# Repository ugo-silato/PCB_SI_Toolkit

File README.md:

# PCB Signal Integrity Toolkit for KiCad
<!-- Donation button: opens my Ko-fi page ("Buy me a Transistor") -->
<!-- The SVG image is hosted in my .github repository, so every README uses the same file -->
<p align="center">
  
</p>

<!-- Short note shown below the button -->
<p align="center">
  Free and open source. If this tool saved you some time,<br>
  a transistor helps me keep developing and sharing new ones ⚡
</p>

A KiCad 10 plugin (Pcbnew) that brings together signal- and power-integrity checks on the board you are designing:

| Tab | What it does |
|---|---|
| **Layout checks** | A smart DRC on the whole board: distance of the decoupling capacitors from the IC supply pins and their ground vias, signal vias that change reference plane without a ground via nearby, stitching via spacing on multi-layer ground, tracks over plane gaps, tracks close to the edge of their reference plane, track width against the current (IPC-2221), isolation between nets above 30 V (IPC-2221), length difference of differential pairs and net groups, dead branches, acute angles, width steps, vias in SMD pads, tombstoning risk, number of vias for the current, crystal placement, overlapping tracks on adjacent layers. Every row is a measure compared with a threshold, marked on the board |
| **Return Path** | Finds tracks that cross gaps in the reference plane underneath, and marks them on the board. **Return map** (HF and DC) shows where the return current of a line flows in the ground, from its loads to the chosen ground exit |
| **DC Current** | Solves the resistive network of tracks and vias: current, IR drop, density and IPC-2221 limit, with one or more loads and a color map |
| **Impedance** | Z0 of every track with a 2D field solver, from the real board stackup (coplanar ground, solder mask) |
| **Diff. pairs** | Differential and common-mode impedance with the field solver (odd/even modes) |
| **Crosstalk** | Parallel runs between different nets and estimated NEXT |
| **openEMS** | 3D FDTD electromagnetic simulation of a line with [openEMS](https://www.openems.de): S-parameters, impedance, TDR/TDT and animated field GIFs |

The interface is available in **English** and **Italian** (Options tab), and every tab has a **?** button with an explanatory drawing.

## Return current map

Give the pad where the current enters and the ground pad where it leaves the board (e.g. the supply ground): the plugin finds the net and every load with a ground pin, also beyond series parts, estimates the current of each one from its type and value (TVS 0, resistor V/R, capacitor V/|Z|, MOSFET gate almost 0, collector V/(series R + pull-up) ...) and lets you check and correct it in a table. The map then shows, layer by layer, where the return flows in planes, coplanar ground and vias, at high frequency (it follows the track) or in DC (minimum resistance), with the share of every ground pin and via. Components and the tracks of the other nets can be drawn over the map to find your way. The currents are an estimate, not a circuit simulation: the result is theoretical.

## Layout checks

A smart DRC that **measures** the layout instead of predicting physical quantities: every row of the table is a fact about the board, with the **Measured** value next to the **Limit** it is compared with, a circle on the board (User.1 = errors, User.2 = warnings) and, for the plane edge, the measured segment with its value. Clicking a row selects the objects in Pcbnew. Currents, voltages and length groups are typed in the tab as `net = value; ...` (wildcards `*` and `?` allowed).

- **Exclude a row**: right click → *Exclude (accepted)*. The row turns grey and goes to the bottom, as KiCad does with excluded DRC errors; it is not counted and not drawn on the board, and it stays excluded in the next runs until the objects involved are edited.
- **Per-board data**: excluded rows and net data are saved next to the board in `board_name.si_toolkit.json`; thresholds stay global.
- **Report**: *Report...* writes `board_name_layout_checks.html` next to the board, with summary, thresholds, a drawing of the board with numbered problems and a zoomed drawing for every problem (print it to PDF from the browser).
- **Test board**: `docs/test_board` has a board with one case for each check and the list of expected rows.

| | |
|---|---|
|  |  |

| | |
|---|---|
| <br>**Plane edge**: Measured = from the edge of the track to where the ground copper of the adjacent layer really ends; Limit = 3 × h (dielectric height). Holes around pads/vias and narrow cuts made by tracks of the plane layer are not an edge. | <br>**Track width**: Measured = actual width; Limit = IPC-2221 width for the current of the net and the allowed temperature rise. |
| <br>**Isolation**: Measured = edge-to-edge copper distance on the same layer between nets more than 30 V apart; Limit = IPC-2221 table (B2 outer, B1 inner). | <br>**Lengths**: skew of the differential pairs (found from the names) and difference from the longest net of each group. |
| <br>**Dead branches**: tracks ending without connecting to anything; Measured = length of the dead branch. Tracks are connected when their copper touches, as in KiCad. | <br>**Acute angles**: segments of the same net meeting at less than 90° (acid traps); micro segments and overlaps are ignored. |
| <br>**Width steps**: a signal net with tracks of different widths on a layer; Measured = (wide − narrow) / narrow in %. Neck-downs at pads are ignored. | <br>**Vias in pads**: via drills inside SMD pads (solder wicking); large thermal pads are ignored. |
| <br>**Tombstoning**: small two-pad parts with one pad flooded in a zone and the other on a track. | <br>**Via current**: Measured = vias at a layer change, Limit = vias needed by IPC-2221 for the current of the net. |
| <br>**Crystal**: tracks of other nets under a crystal, and length of the crystal–IC tracks. | <br>**Overlapping tracks**: different nets one over the other on adjacent layers; Measured = overlap length. |

## Installation

### From the Plugin and Content Manager (recommended)
1. Download `si_toolkit_pcm_x.y.z.zip` from the [Releases](../../releases) page.
2. In KiCad open **Plugin and Content Manager → Install from File...**, choose the zip and press **Apply Pending Changes**.
3. Restart Pcbnew: the plugin appears in the toolbar and in **Tools → External Plugins**.

### Manually
Copy the `si_toolkit` folder into the KiCad user plugin folder, for example
`Documents\KiCad\10.0\scripting\plugins\si_toolkit`, then restart Pcbnew.

Settings are stored in the KiCad user configuration folder (`si_toolkit_settings.json`), so they survive plugin updates.

## openEMS (optional, only for the openEMS tab)
The plugin does **not** install openEMS. All other tabs work with KiCad's own Python.

1. Download openEMS for Windows from the official openEMS releases and extract it (e.g. `D:\Programs\openEMS`).
2. Install a 64-bit Python supported by that openEMS release.
3. In the **Options** tab set the Python and the openEMS folder, then press **Check openEMS**.
4. If something is missing (numpy, h5py, matplotlib, or the CSXCAD/openEMS modules from the `.whl` files of the openEMS distribution), **Install missing packages** installs it after confirmation.

## The tabs at a glance

| | |
|---|---|
|  |  |
|  |  |
|  |  |

## Limits
- Except for openEMS the analyses are quasi-static: they are meant to compare options and find problems, not to replace measurements.
- With *Copper zones = zero resistance* the DC result is optimistic; without it, pessimistic.
- **Layout checks**: the default thresholds are good-practice rules for a generic board (decoupling capacitor within 3 mm of the pin, error beyond 8 mm; ground via within 1 mm of a GND pad; return via within 2 mm of a signal via that changes reference plane; stitching vias every 10 mm; plane gaps from 5 mm; plane edge at least 3 h from the track; 10 °C track temperature rise; pair skew 0.5 mm, groups within 2 mm; dead branches from 1 mm; acute angles below 90°; width steps above 25 %; crystal–IC tracks up to 10 mm; overlapping tracks from 5 mm). Currents, voltages and length groups are typed in the tab as `net = value; ...` (wildcards allowed); voltages are otherwise read from the net names. Known limits: the capacitor considered is the nearest one on the same supply, whatever its value; the layer change check covers all the signals, slow ones too, so many warnings can be ignored; one stitching spacing for the whole board (RF areas such as a 1.5 GHz GNSS need about 5 mm: run a second check); only ground planes are considered as reference; distances are straight-line; stitching areas follow a 1-2 mm grid; the plane edge is measured to the real ground fill, ignoring cuts up to 2 mm wide made by the tracks of the plane layer (on a two-layer board h is about 1.5 mm, so the 3 h limit is about 4.5 mm and also reports tracks a few mm from the board edge); the track width check assumes the whole current of the net on every track; IPC-2221 isolation distances are a PCB design minimum, mains safety standards (IEC 62368-1, IEC 60664) ask for more; lengths include every branch of the net; width steps, dead branches, acute angles and overlapping tracks look at all the signal nets, slow ones too; a crystal is recognized only from the Y reference or the footprint name.
- Tested on KiCad 10 under Windows.

## For developers
- `si_toolkit/tools/build_pcm.py` builds the Plugin Manager package (increase `VERSION` first).
- `si_toolkit/tools/make_help_images.py` regenerates the help drawings (needs matplotlib).
- `si_toolkit/tools/make_test_board.py` regenerates the test board in `docs/test_board` (needs the pcbnew module, e.g. KiCad's Python).
- The version is written only in `si_toolkit/common/version.py`.
- UI texts are written in Italian in the code and translated through `common/i18n_en.py`.

## What's new in 1.2.0

- **Layout checks** tab: a smart DRC on the whole board with 16 checks, every row a measure compared with a limit (with its unit) and marked on the board: decoupling, layer change, stitching vias, plane gap, plane edge (measured to the real ground fill), track width vs current, isolation (IPC-2221), lengths (pair skew and groups), dead branches, acute angles, width steps, vias in SMD pads, tombstoning, via current, crystal placement, overlapping tracks on adjacent layers.
- Rows can be **excluded** with a right click (greyed, as in KiCad's DRC) and stay excluded in the next runs.
- **Per-board data**: excluded rows, currents, voltages and length groups saved next to the board (`board_name.si_toolkit.json`).
- **HTML report** with summary, thresholds and a drawing of every reported point (printable to PDF).
- **Test board** in `docs/test_board` with one case for each check and the expected rows.
- **All / None** buttons for the checks; help with one drawing per check, in English and Italian.
- Return Path tab: return current map (HF and DC) with loads found and estimated automatically.

## License
[MIT](LICENSE) © 2026 Ugo Silato

## Code comments translated by Claude
---

## In italiano

Plugin per KiCad 10 che raccoglie in un'unica finestra i controlli di integrità del segnale e dell'alimentazione: **Controlli layout** (un DRC ragionato su tutta la scheda: distanza dei condensatori di disaccoppiamento e loro via di massa, cambi di layer senza via di ritorno, passo delle via di stitching, tracce sopra interruzioni del piano, tracce vicine al bordo del piano, larghezza delle tracce rispetto alla corrente, distanze di isolamento fra net ad alta tensione, lunghezze di coppie differenziali e gruppi di net, rami morti, angoli acuti, cambi di larghezza, via nei pad SMD, rischio di tombstoning, numero di via per la corrente, posizione del quarzo, tracce sovrapposte su layer adiacenti; soglie predefinite pensate per una scheda generica, limiti spiegati nella guida del plugin; ogni riga riporta la *Misura* trovata sulla scheda e il *Limite* con cui è confrontata, e la guida ha un disegno per ogni controllo che mostra cosa si misura; una riga accettata si esclude con il clic destro e diventa grigia come nel DRC di KiCad; righe escluse e dati delle net si salvano accanto alla scheda; il pulsante *Rapporto...* crea una pagina HTML, stampabile in PDF, con i disegni dei punti segnalati; in `docs/test_board` c'è una scheda di prova con un caso per ogni controllo), **Return Path** (piano di riferimento interrotto sotto le tracce, con mappa della corrente di ritorno in alta frequenza e in continua, dall'ingresso fino all'uscita di massa, con correnti dei carichi stimate dal tipo e dal valore dei componenti), **Corrente DC** (corrente, caduta IR e limite IPC-2221 con più carichi e mappa a colori), **Impedenza** e **Coppie differenziali** con risolutore di campo 2D dallo stackup reale, **Crosstalk** e simulazione elettromagnetica 3D con **openEMS** (parametri S, impedenza, TDR/TDT, GIF del campo).

**Installazione:** scarica `si_toolkit_pcm_x.y.z.zip` dalla pagina [Releases](../../releases) e in KiCad usa *Gestore di plugin e contenuti → Installa da file...*. In alternativa copia la cartella `si_toolkit` in `Documenti\KiCad\10.0\scripting\plugins`.

**openEMS** va installato a parte (serve solo alla scheda openEMS): nella scheda *Opzioni* indica Python e cartella di openEMS e premi *Verifica openEMS*, che dice cosa manca e può installare i pacchetti mancanti.

**Novità della 1.2.0:** scheda *Controlli layout* con 16 controlli (misura e limite per ogni riga), righe escludibili con il clic destro, dati salvati per ogni scheda, rapporto HTML/PDF con i disegni, scheda di prova in `docs/test_board`, pulsanti *Tutti* / *Nessuno*, mappa della corrente di ritorno nella scheda Return Path.

La lingua dell'interfaccia si sceglie nella scheda *Opzioni* (inglese predefinito, oppure italiano); ogni scheda ha un pulsante **?** con un disegno che spiega i dati da inserire.

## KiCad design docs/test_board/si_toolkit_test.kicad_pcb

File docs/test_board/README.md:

# Test board of the Layout checks

`si_toolkit_test.kicad_pcb` is a 120 × 90 mm two-layer board with one case for
every check of the **Layout checks** tab, plus a few cases that must **not** be
reported. Its net data (`+5V=2; VIN=5`, group `SD_*`) are in
`si_toolkit_test.si_toolkit.json`, which the plugin reads automatically.
Every case is labelled on the silkscreen with the number of its check.

Open the board in Pcbnew, fill the zones (**B**), open the plugin and press
**Run checks** with the default thresholds. The board was generated by
`si_toolkit/tools/make_test_board.py`.

## Expected rows (21)

| # | Check | Object | Measured / Limit | What the case is |
|---|---|---|---|---|
| 1 | Decoupling | U1.1 (+3V3) | 10.2 / 3 mm (error) | the only capacitor C1 is 10 mm from the supply pin |
| 2 | Layer change | SIG_LC | 5.6 / 2 mm (error) | signal via with no ground via close |
| 3 | Stitching vias | F.Cu + B.Cu (GND) | 29.4 / 7.1 mm (error) | lower right corner left without vias |
| 3 | Stitching vias | F.Cu + B.Cu (GND) | ≈11 / 7.1 mm (warning) | around the plane slot, where the vias are kept away on purpose |
| 4 | Plane gap | PG_SIG | 8 / 5 mm (error) | track over an 8 mm slot of the bottom plane |
| 4 | Plane gap | NA, NB | 19–20 / 5 mm (warnings) | side effect of case 16: each track removes the plane of the other |
| 5 | Plane edge | EDGE_SIG | 0.57 / 4.59 mm (error) | track 1.2 mm from the top board edge |
| 6 | Track width | +5V | 0.25 / 0.78 mm (error) | 0.25 mm track with 2 A |
| 7 | Isolation | GND / HV_400V | 0.30 / 2.5 mm (error) | the top ground pour comes 0.3 mm from the 400 V track |
| 8 | Lengths | USB | 3.5 / 0.5 mm (error) | USB_DM 3.5 mm longer than USB_DP |
| 8 | Lengths | SD_D1 | 5 / 2 mm (error) | SD_D1 5 mm shorter than SD_D0 in group SD_* |
| 9 | Dead branches | DATA | 3 / 1 mm (warning) | 3 mm branch ending in nothing |
| 10 | Acute angles | ACUTE | 17° / 90° (warning) | the track comes back at 17° (RIGHT, at 90°, is not reported) |
| 11 | Width steps | WSTEP | 67 / 25 % (error) | 0.25 mm then 0.15 mm (NECK, a neck-down at the pad, is not reported) |
| 12 | Vias in pads | R3.1 (VIP) | – (warning) | via drill inside the SMD pad |
| 13 | Tombstoning | C9 | – (warning) | GND pad in a zone with solid connection, other pad on a track |
| 14 | Via current | VIN | 2 / 3 via (warning) | 5 A through two 0.3 mm vias |
| 15 | Crystal | XIN | 26 / 10 mm (error) | 26 mm of tracks between Y1 and U15 |
| 15 | Crystal | Y1 / OTHER | – (error) | track of another net under the crystal |
| 16 | Overlapping tracks | NA / NB | 20 / 5 mm (warning) | NA on top over NB on the bottom for 20 mm |

The report (**Report...**) of this board shows all of them with a drawing.

---

## In italiano

Scheda di prova a due layer con un caso per ciascuno dei 16 controlli della
scheda **Controlli layout** (più alcuni casi che **non** devono essere segnalati).
I dati delle net sono nel file `si_toolkit_test.si_toolkit.json`, letto in
automatico dal plugin; ogni caso ha sulla serigrafia il numero del suo controllo.
Apri la scheda, riempi le zone (**B**) e lancia i controlli con le soglie
predefinite: le righe attese sono quelle della tabella qui sopra (21 righe).

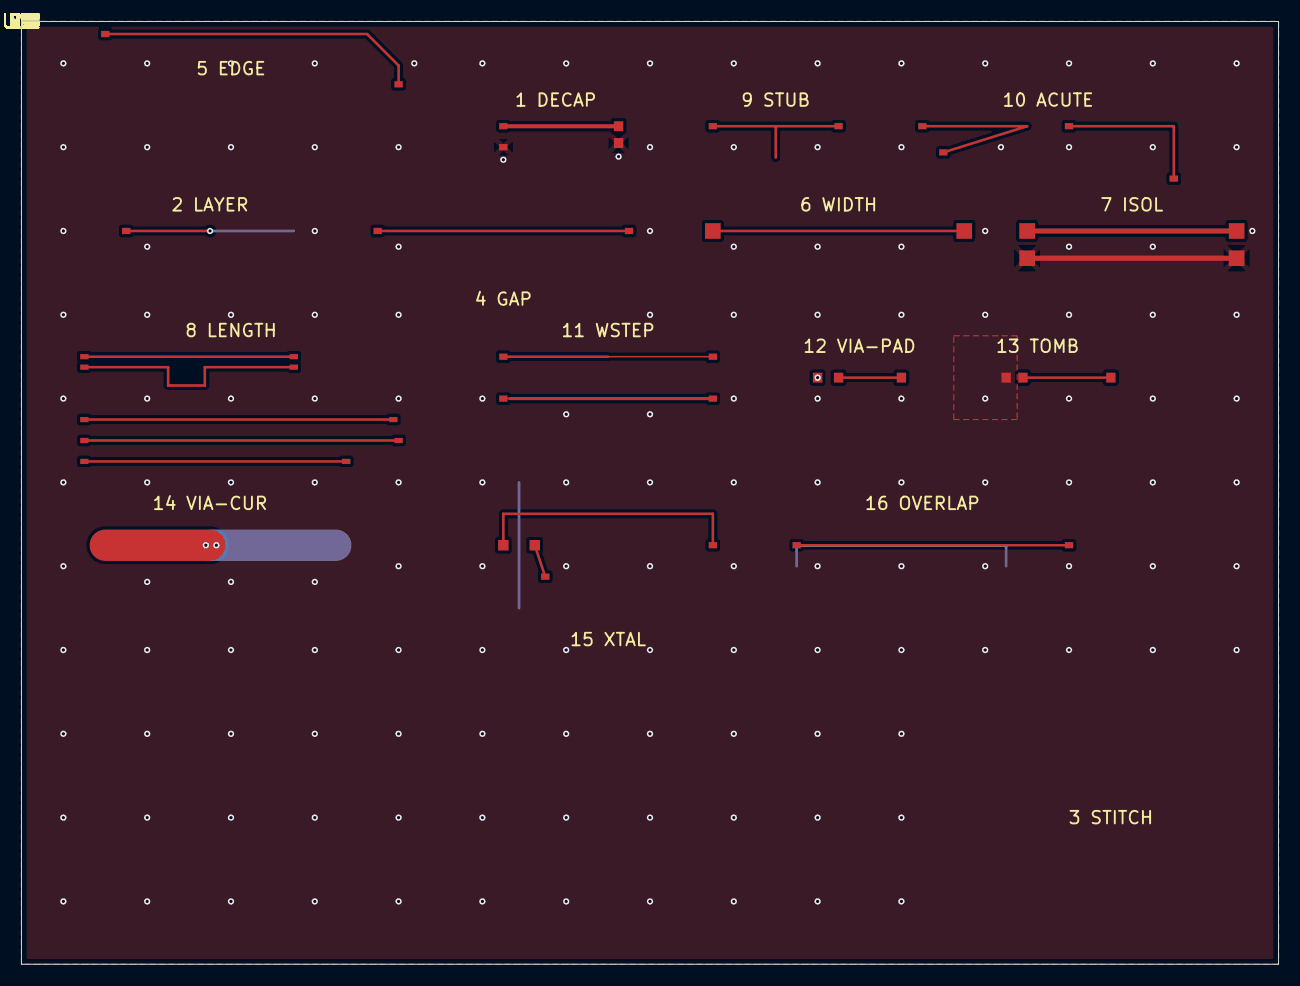
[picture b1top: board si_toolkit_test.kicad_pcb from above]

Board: 2 copper layers, 120.0 x 90.0 mm, 29 parts (0 on the bottom side), 25 nets.

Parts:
C1: C1
C9: C9
J1: J1
J2: J2
J3: J3
J4: J4
R2: R2
R3: R3
R4: R4
R5: R5
U1: U1
U2: U2
U3: U3
U4: U4
U5: U5
U6: U6
U7: U7
U8: U8
U9: U9
U10: U10
U11: U11
U12: U12
U13: U13
U14: U14
U15: U15
U16: U16
U17: U17
U18: U18
Y1: Y1

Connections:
+3V3: C1.1, U1.1
+5V: J1.1, J1.2
ACUTE: U3.1, U3.2
DATA: R2.1, U2.1
EDGE_SIG: U10.1, U10.2
GND: C1.2, C9.1, J2.3, J2.4, U1.2
HV_400V: J2.1, J2.2
NA: U17.1, U17.2
NB: U18.1, U18.2
NECK: U14.1, U14.2
OTHER: U16.1, U16.2
PG_SIG: U7.1, U7.2
RIGHT: U4.1, U4.2
SD_CLK: U11.1, U12.1
SD_D0: U11.2, U12.2
SD_D1: U11.3, U12.3
SIGX: C9.2, R5.1
SIG_LC: U5.1, U6.1
USB_DM: U8.2, U9.2
USB_DP: U8.1, U9.1
VIN: J3.1, J4.1
VIP2: R3.2, R4.1
WSTEP: U13.1, U13.2
XIN: U15.1, Y1.1
XOUT: U15.2, Y1.2
